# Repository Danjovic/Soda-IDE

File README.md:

# SODA IDE
Compact Flash Card Interface for MSX based on [SC729 RCBus Compact Flash Module]( https://smallcomputercentral.com/sc729-rcbus-compact-flash-module/) originally designed by [Tadeusz Pycio](http://www.vtsys.pl/interface-compact-flash/) and [Beer IDE 232](https://github.com/b3rendsh/msxdos2s) by b3rendsh 

## Printed circuit Boards:
### For Konami Case

#### Version 1

#### Version 2

### For Patola Case
#### Version 2

### BILL OF MATERIALS

#### Semiconductors

| Reference | Value | Description            |
|:---:|:-------: |:----------------------------------------- |
|  U1 | 27C512   | EEPROM 64Kb x 8 (512kbits)                |
|  U2 | 74HCT32  | TTL chip, can be either LS, HC or HCT     |
|  U3 | 74HCT74  | TTL chip, can be either LS, HC or HCT     |
|  U4 | 74HCT138 | TTL chip, can be either LS, HC or HCT     |
|  U5 | 74HC245  | TTL chip, can be either LS, HC or HCT     |
|  Q1 | BC548    | NPN transistor                            |
| LD1 | --       |     Diameter 3.0mm, Red                   |
|  D1 | 1N4148   | Fast diode, Sillicon (alternatives 1N914) |

#### Capacitors

| Reference | Value | Description            |
|:---:|:-------: |:----------------------------------------- |
|C1,C2,C3,C4,C5| 100nF | Capacitor, Ceramic disc or Polyester |
|C6| 100uF/16V | Electrolytic Capacitor (preferrable low profile) |
		
#### Resistors		
| Reference | Value | Description            |
|:---:|:-------: |:----------------------------------------- |
| R1,R2,R3,R6 | 4K7 | Resistor, ¼ Watt | 
| R4 | 1K | Resistor, ¼ Watt | 
| R5 | 10K | Resistor, ¼ Watt | 
		
#### Miscellaneous		
| Reference | Value | Description            |
|:---:|:-------: |:----------------------------------------- |
|SW1	| -- | SPDT Switch, slide, right angle (reference OS102011MA1QN1) |
|CN1	| -- | Printed Circuit Board. Gerbers for Konami [V1](https://github.com/Danjovic/Soda-IDE/tree/main/hardware/V1/Gerber), [V2](https://github.com/Danjovic/Soda-IDE/tree/main/hardware/V2/SodaIDE_v2_konami_case/pcbway_production/2025-02-08-15-33-09), Patola [V2](https://github.com/Danjovic/Soda-IDE/tree/main/hardware/V2/SodaIDE_v2_patola_case/pcbway_production/2025-02-08-15-50-29) |
|JP1	| -- | Pin Header, 1x3 pin, pitch 2.54mm, straight (Vertical) |
|JP2,JP3,JP4 | -- | Pin Header, 1x2 pin, pitch 2.54mm, straight (Vertical) |

#### 44 pin CF adapter option		
| J1	|	Pin Header, 2x22 pin, pitch 2.0mm, right angle (Horizontal) |
|:---:| :----------------------------------------- |
		
#### 40 pin CF adapter option		
|J2	|	Pin Header, 2x20 pin, pitch 2.54mm, right angle (Horizontal)
|:---:| :----------------------------------------- |
		
#### CF Socket Option		
|J3	|	CF Card Connector (reference 3M_N7E50-E516xx-30)
|:---:| :----------------------------------------- |

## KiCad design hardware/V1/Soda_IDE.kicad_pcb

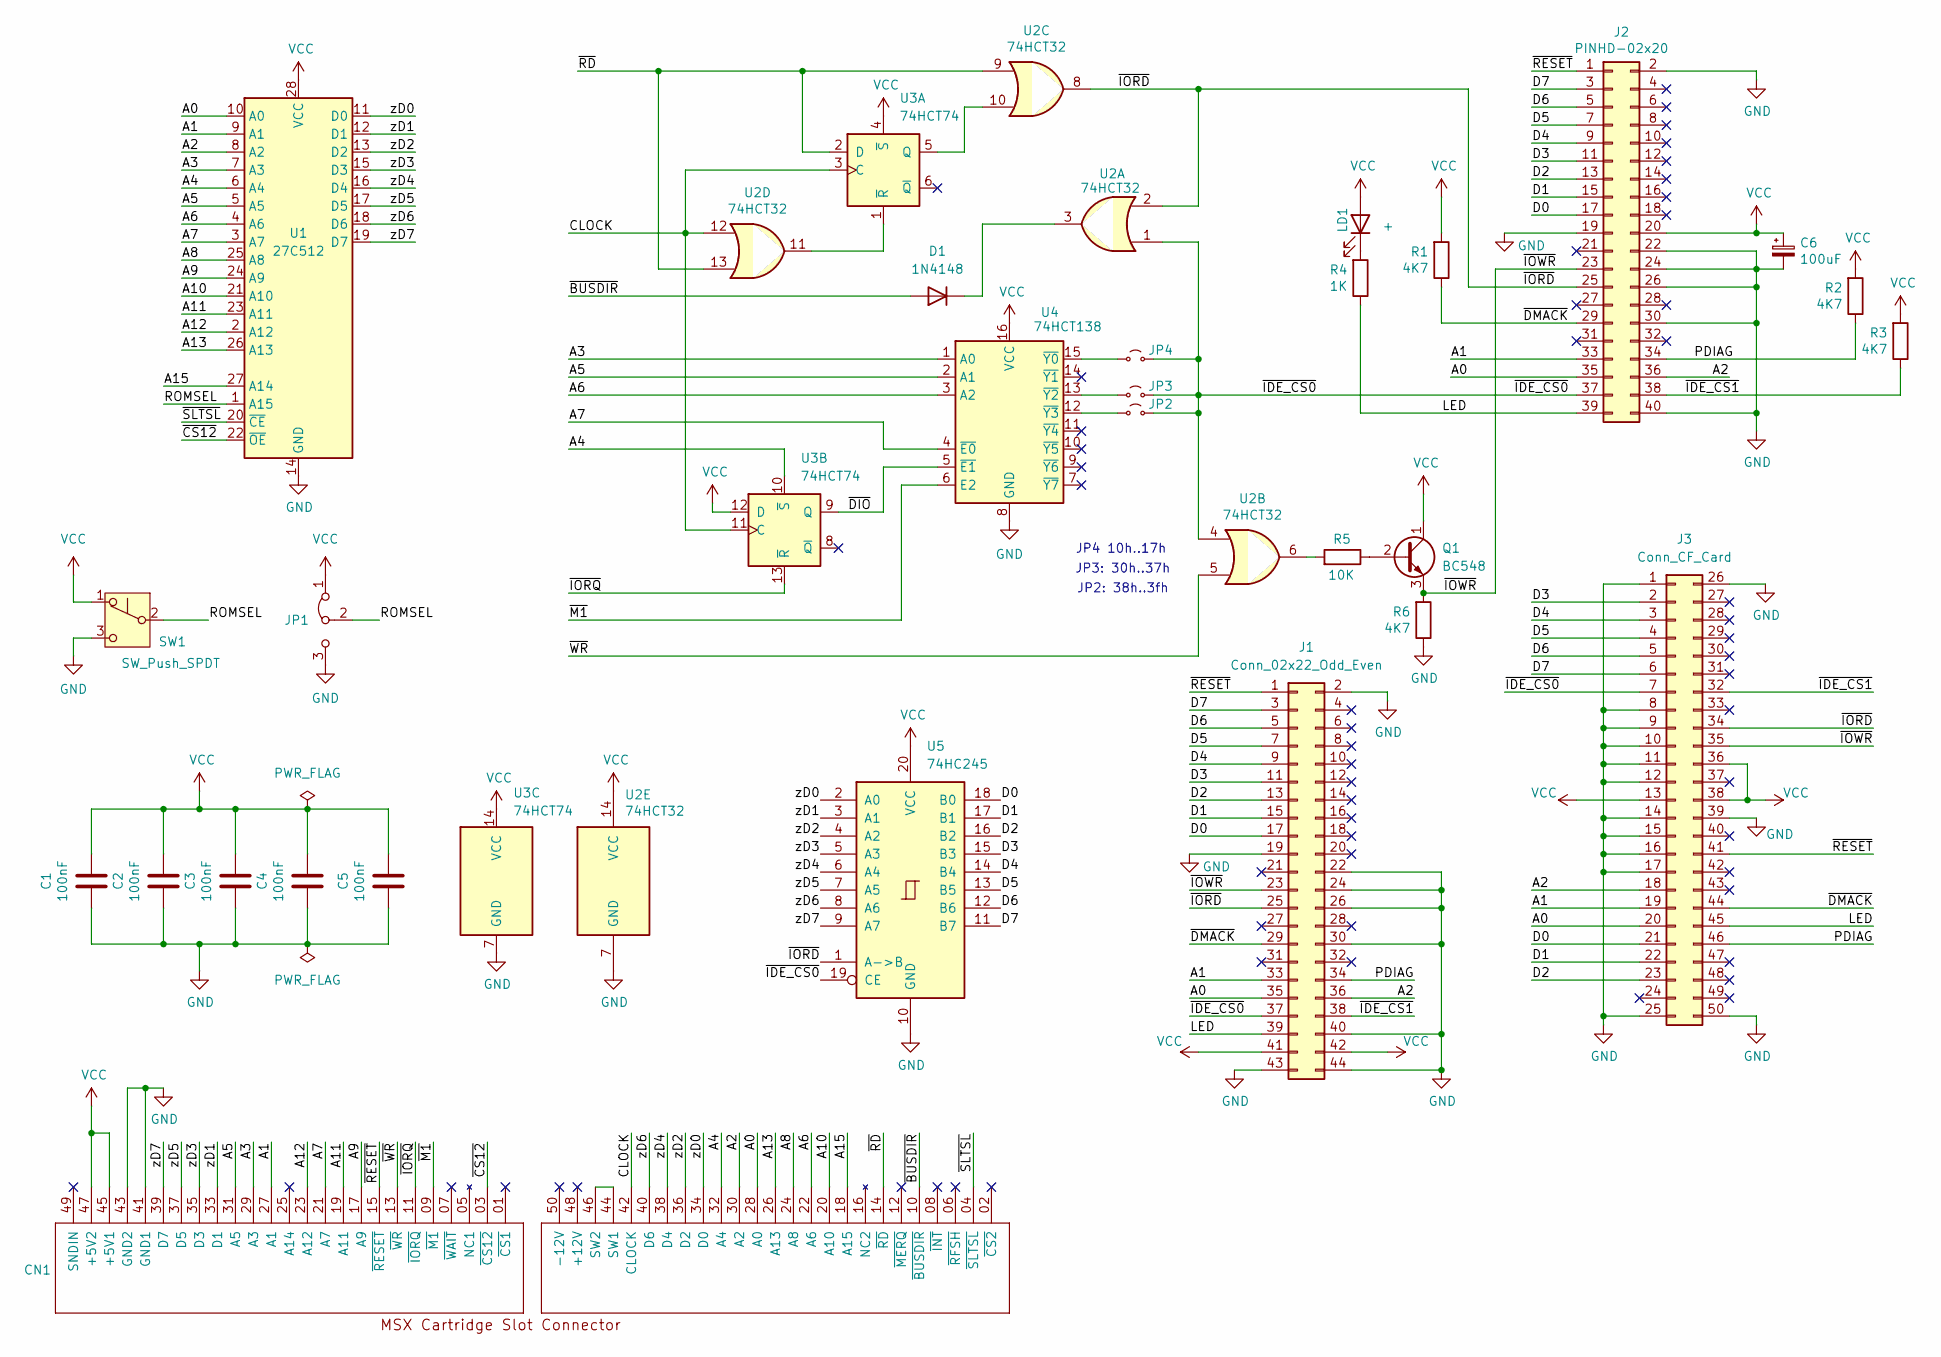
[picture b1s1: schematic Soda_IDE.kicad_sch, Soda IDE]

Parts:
C1, C2, C3, C4, C5: 100nF; C_Disc_D4.7mm_W2.5mm_P5.00mm
C6: 100uF; CP_lying
CN1: MSX_SLOT_CON; Cart_Konami
D1: 1N4148; D_DO-35_SOD27_P7.62mm_Horizontal
J1: Conn_02x22_Odd_Even; PinHeader_2x22_P2.00mm_Horizontal
J2: PINHD-02x20; PinHeader_2x20_P2.54mm_Horizontal
J3: Conn_CF_Card; CF-Card_3M_N7E50-E516xx-30
JP1: PIN_1x3; PinHeader_1x03_P2.54mm_Vertical
JP2, JP3, JP4: Jumper_2_Small_Open; PinHeader_1x02_P2.54mm_Vertical
LD1: +; LED_D3.0mm
Q1: BC548; TO-92_Inline
R1, R2, R3, R6: 4K7; R_Axial_DIN0207_L6.3mm_D2.5mm_P7.62mm_Horizontal
R4: 1K; R_Axial_DIN0207_L6.3mm_D2.5mm_P7.62mm_Horizontal
R5: 10K; R_Axial_DIN0207_L6.3mm_D2.5mm_P7.62mm_Horizontal
SW1: SW_Push_SPDT; SW_Slide_SPDT_Angled_CK_OS102011MA1Q
U1: 27C512; DIP-28_W15.24mm
U2: 74HCT32; DIP-14_W7.62mm
U3: 74HCT74; DIP-14_W7.62mm
U4: 74HCT138; DIP-16_W7.62mm
U5: 74HC245; DIP-20_W7.62mm

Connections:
/A0: CN1.28 (A0), J1.35, J2.35, J3.20, U1.10 (A0)
/A1: CN1.27 (A1), J1.33, J2.33, J3.19, U1.9 (A1)
/A2: CN1.30 (A2), J1.36, J2.36, J3.18, U1.8 (A2)
/A3: CN1.29 (A3), U1.7 (A3), U4.1 (A0)
/A4: CN1.32 (A4), U1.6 (A4), U3.10 (~S)
/A5: CN1.31 (A5), U1.5 (A5), U4.2 (A1)
/A6: CN1.22 (A6), U1.4 (A6), U4.3 (A2)
/A7: CN1.21 (A7), U1.3 (A7), U4.4 (~E0)
/A8: CN1.24 (A8), U1.25 (A8)
/A9: CN1.17 (A9), U1.24 (A9)
/A10: CN1.20 (A10), U1.21 (A10)
/A11: CN1.19 (A11), U1.23 (A11)
/A12: CN1.23 (A12), U1.2 (A12)
/A13: CN1.26 (A13), U1.26 (A13)
/A15: CN1.18 (A15), U1.27 (A14)
/CLOCK: CN1.42 (CLOCK), U2.12, U3.3 (C), U3.11 (C)
/D0: J1.17, J2.17, J3.21, U5.18 (B0)
/D1: J1.15, J2.15, J3.22, U5.17 (B1)
/D2: J1.13, J2.13, J3.23, U5.16 (B2)
/D3: J1.11, J2.11, J3.2, U5.15 (B3)
/D4: J1.9, J2.9, J3.3, U5.14 (B4)
/D5: J1.7, J2.7, J3.4, U5.13 (B5)
/D6: J1.5, J2.5, J3.5, U5.12 (B6)
/D7: J1.3, J2.3, J3.6, U5.11 (B7)
/LED: J1.39, J2.39, J3.45, R4.1
/PDIAG: J1.34, J2.34, J3.46, R2.1
/ROMSEL: JP1.2 (C), SW1.2 (B), U1.1 (A15)
/zD0: CN1.34 (D0), U1.11 (D0), U5.2 (A0)
/zD1: CN1.33 (D1), U1.12 (D1), U5.3 (A1)
/zD2: CN1.36 (D2), U1.13 (D2), U5.4 (A2)
/zD3: CN1.35 (D3), U1.15 (D3), U5.5 (A3)
/zD4: CN1.38 (D4), U1.16 (D4), U5.6 (A4)
/zD5: CN1.37 (D5), U1.17 (D5), U5.7 (A5)
/zD6: CN1.40 (D6), U1.18 (D6), U5.8 (A6)
/zD7: CN1.39 (D7), U1.19 (D7), U5.9 (A7)
/~BUSDIR: CN1.10 (~BUSDIR), D1.2 (A)
/~CS12: CN1.03 (~CS12), U1.22 (~OE)
/~DIO: U3.9 (Q), U4.5 (~E1)
/~DMACK: J1.29, J2.29, J3.44, R1.1
/~IDE_CS0: J1.37, J2.37, J3.7, JP2.2 (B), JP3.2 (B), JP4.2 (B), U2.1, U2.4, U5.19 (CE)
/~IDE_CS1: J1.38, J2.38, J3.32, R3.1
/~IORD: J1.25, J2.25, J3.34, U2.2, U2.8, U5.1 (A->B)
/~IORQ: CN1.11 (~IORQ), U3.13 (~R)
/~IOWR: J1.23, J2.23, J3.35, Q1.3 (E), R6.2
/~M1: CN1.09 (~M1), U4.6 (E2)
/~RD: CN1.14 (~RD), U2.9, U2.13, U3.2 (D)
/~RESET: CN1.15 (~RESET), J1.1, J2.1, J3.41
/~SLTSL: CN1.04 (~SLTSL), U1.20 (~CE)
/~WR: CN1.13 (~WR), U2.5
GND: C1.2, C2.2, C3.2, C4.2, C5.2, C6.2, CN1.41 (GND1), CN1.43 (GND2), J1.2, J1.19, J1.22, J1.24, J1.26, J1.30, J1.40, J1.43, J1.44, J2.2, J2.19, J2.22, J2.24, J2.26, J2.30, J2.40, J3.1, J3.8, J3.9, J3.10, J3.11, J3.12, J3.14, J3.15, J3.16, J3.17, J3.25, J3.26, J3.39, J3.50, JP1.3 (B), R6.1, SW1.3 (C), U1.14 (GND), U2.7 (GND), U3.7 (GND), U4.8 (GND), U5.10 (GND)
unnamed: CN1.44 (SW1), CN1.46 (SW2)
unnamed: D1.1 (K), U2.3
unnamed: JP2.1 (A), U4.12 (~Y3)
unnamed: JP3.1 (A), U4.13 (~Y2)
unnamed: JP4.1 (A), U4.15 (~Y0)
unnamed: LD1.1 (K), R4.2
unnamed: Q1.2 (B), R5.1
unnamed: R5.2, U2.6
unnamed: U2.10, U3.5 (Q)
unnamed: U2.11, U3.1 (~R)
VCC: C1.1, C2.1, C3.1, C4.1, C5.1, C6.1, CN1.45 (+5V1), CN1.47 (+5V2), J1.41, J1.42, J2.20, J3.13, J3.36, J3.38, JP1.1 (A), LD1.2 (A), Q1.1 (C), R1.2, R2.2, R3.2, SW1.1 (A), U1.28 (VCC), U2.14 (VCC), U3.4 (~S), U3.12 (D), U3.14 (VCC), U4.16 (VCC), U5.20 (VCC)

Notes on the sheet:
JP4 10h..17h
JP3: 30h..37h
JP2: 38h..3fh

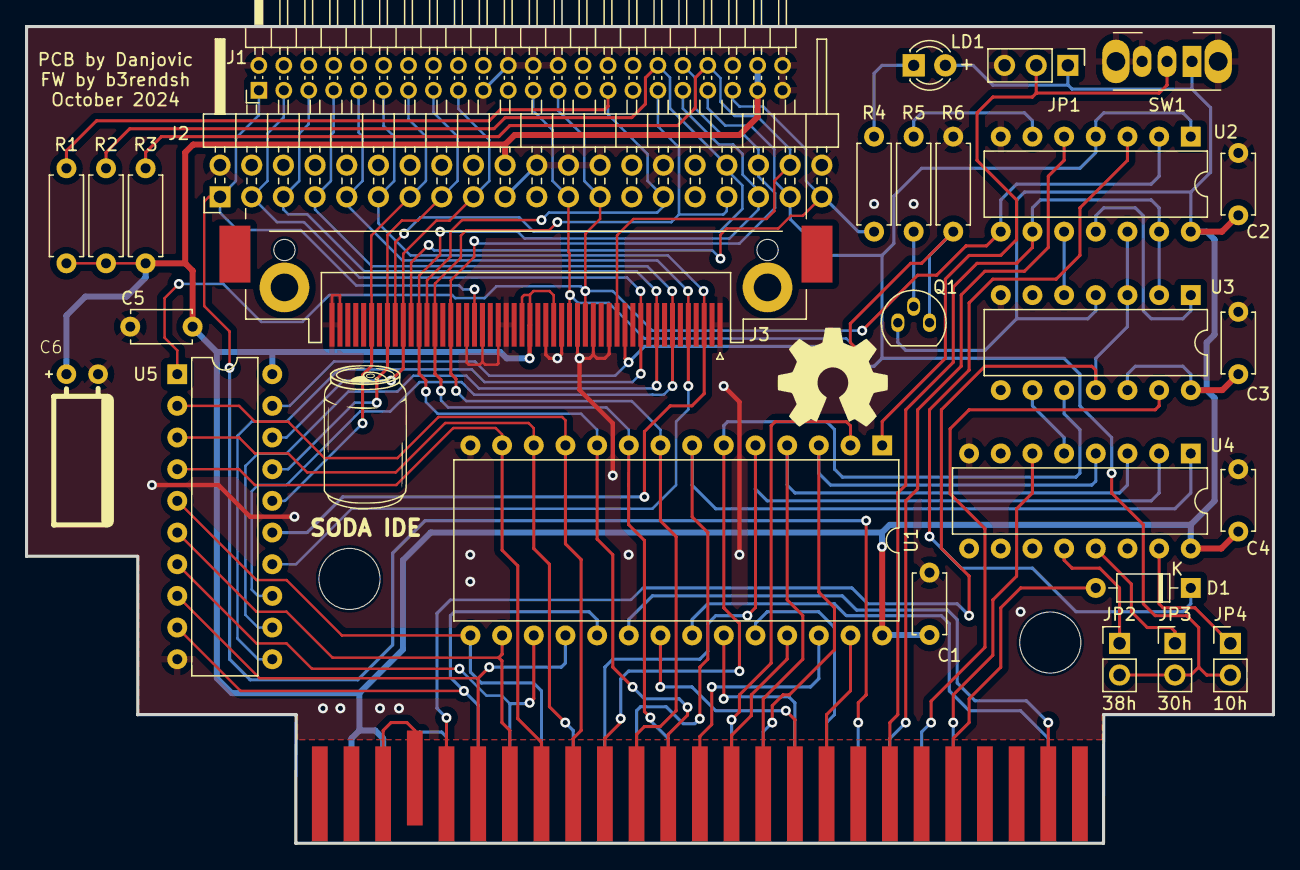
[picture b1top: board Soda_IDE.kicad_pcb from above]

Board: 2 copper layers, 100.0 x 65.5 mm, 29 parts (0 on the bottom side), 61 nets.

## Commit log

2024-10-25 fixes and udpates
2024-10-25 fixes and updates
2024-10-25 conventional jumpers for address selection
2024-10-25 updated image
2024-10-29 Added buffer to data lines
2024-10-30 updated board
2024-11-07 Reduced board width to be within 100mm
2025-02-08 New boards for Konami and Patola cases
2025-02-08 Erased duplicate Files
